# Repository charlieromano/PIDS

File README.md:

<h1> PIDS</h1>

Proyecto PIDS, CESE 2020. 

<h3> Índice </h3>

<hr>

1. [Iniciar Repositorio](#iniciar)

 	1.1. [Clonar repositorio](#clonar)	
 	1.2. [Incluir submódulos](#submodulos)
 	1.3. [Instalar software](#software)
 	
 		1.3.1 [openocd](#openocd)
 		1.3.2 [gcc arm](#gcc)
 		1.3.3 [EDU-CIAA](#educiaa)
 		1.3.4 [Troubleshooting ](#troubleshooting)
 			1.3.4.1 [Troubleshooting gcc-arm](#gcc-arm)
 			1.3.4.2 [Troubleshooting Ubuntu 22](#ubuntu22)
 			1.3.4.3 [Troubleshooting Virtualbox Ubuntu 22 Guest OS](#guestOS)
 			1.3.4.4 [Troubleshooting FTDI driver](#ftdi)
 	
 	1.4. [Crear un programa](#create)
 	1.5. [Seleccionar un programa](#select)

2. [Ejemplos usando UART](#UART)

3. [Ejemplos usando Máquinas de Estado y RTOS](#fsm)

4. [Ejemplos usando Objeto Activo](#ActiveObject)

5. [Ejemplos usando Objeto Activo con Interrupciones](#ActiveObjectISR)

6. [Ejemplos usando Objeto Activo con Interrupciones y UART](#ActiveObjectUART)

<hr>

## Ejemplos usando UART 

Link: https://github.com/charlieromano/PIDS/tree/main/Scripts/UART_RTOS

<hr>

## Ejemplos usando Máquinas de Estado y RTOS  

Link: https://github.com/charlieromano/PIDS/tree/main/Scripts/RTOS_fsm

<hr>

## Ejemplos usando Objeto Activo  

Link: https://github.com/charlieromano/PIDS/tree/main/Scripts/ActiveObject

<hr>

## Ejemplos usando Objeto Activo con Interrupciones  

Link: https://github.com/charlieromano/PIDS/tree/main/Scripts/ActiveObject_ISR_TEC

<hr>

## Ejemplos usando Objeto Activo con Interrupciones y UART 

Link: https://github.com/charlieromano/PIDS/tree/main/Scripts/ActiveObject_ISR_UART

<hr>

## 1. Iniciar Repositorio 

Para ejecutar el software desarrollado en este repositorio hace falta incluir submódulos y también software adicional relacionado a la plataforma EDU-CIAA. Para esto, se explican los pasos:

1. Clonar este repositorio
2. Incluir submódulos
3. Instalar software

### 1.1: Clonar este repositorio 

```bash
git clone https://github.com/charlieromano/PIDS.git
```

### 1.2: Incluir submódulos 

```bash
cd PIDS
cd Scripts
git submodule add https://github.com/epernia/firmware_v3.git    #Agrega firmware_v3 como submodulo
git submodule init
git submodule update

```

### 1.3: Instalar software 

Si tiene todo el software instalado puede saltar a la sección siguiente de Crear un Programa.

#### 1.3.1 Instalar openocd 

```bash
sudo apt install openocd
```

#### 1.3.2 Instalar gcc-arm-none-eab 

```bash
sudo apt install gcc-arm-none-eabi

```
Si todo sale ok saltar a la sección crear programa.

#### 1.3.3  Instalar software EDU-CIAA (opcional) 

Debe descargar de [releases](https://github.com/epernia/software/releases/tag/r1.1.0) la versión para Windows o Linux.

Link: https://github.com/epernia/software/releases/tag/r1.1.0

Descomprimir la carpeta en una ruta conocida, sin espacios y con los permisos adecuados. Se recomiendan:

- **Windows**. C:\CIAA\
- **Linux**. $HOME/CIAA/

Luego ingresar a la carpeta y ejecutar el lanzador de apliaciones. 

#### 1.3.4 Troubleshooting  

#### 1.3.4.1 Troubleshooting gcc-arm-none-eabi 

Este fue el primer fail al intentar compilar un programa con el comando "make download". Para solucionarlo, en la instalación de ubuntu 20 LTS lo que hice fue seguir el siguiente hilo: https://askubuntu.com/questions/1243252/how-to-install-arm-none-eabi-gdb-on-ubuntu-20-04-lts-focal-fossa

Básicamente hice lo siguiente:

```bash
sudo apt remove gcc-arm-none-eabi
```

Download latest version  (Linux x86_64 Tarball) [from their website](https://developer.arm.com/tools-and-software/open-source-software/developer-tools/gnu-toolchain/gnu-rm/downloads), check its MD5. Unpack it into some directory. I used /usr/share/ : 

```bash
sudo tar xjf gcc-arm-none-eabi-your-version.bz2 -C /usr/share/
```

Create links so that binaries are accessible system-wide:

```bash
sudo ln -s /usr/share/<gcc-arm-none-eabi-your-version>/bin/arm-none-eabi-gcc /usr/bin/arm-none-eabi-gcc 
...
```

Para mi instalación, (ubuntu 20 LTS) tuve que ejecutar los siguientes links:

```bash
sudo ln -s /usr/share/gcc-arm-none-eabi-10-2020-q4-major-x86_64-linux/gcc-arm-none-eabi-10-2020-q4-major/bin/arm-none-eabi-gcc /usr/bin/arm-none-eabi-gcc
sudo ln -s /usr/share/gcc-arm-none-eabi-10-2020-q4-major-x86_64-linux/gcc-arm-none-eabi-10-2020-q4-major/bin/arm-none-eabi-g++ /usr/bin/arm-none-eabi-g++
sudo ln -s /usr/share/gcc-arm-none-eabi-10-2020-q4-major-x86_64-linux/gcc-arm-none-eabi-10-2020-q4-major/bin/arm-none-eabi-gdb /usr/bin/arm-none-eabi-gdb
sudo ln -s /usr/share/gcc-arm-none-eabi-10-2020-q4-major-x86_64-linux/gcc-arm-none-eabi-10-2020-q4-major/bin/arm-none-eabi-size /usr/bin/arm-none-eabi-size
sudo ln -s /usr/share/gcc-arm-none-eabi-10-2020-q4-major-x86_64-linux/gcc-arm-none-eabi-10-2020-q4-major/bin/arm-none-eabi-objcopy /usr/bin/arm-none-eabi-objcopy
sudo ln -s /usr/share/gcc-arm-none-eabi-10-2020-q4-major-x86_64-linux/gcc-arm-none-eabi-10-2020-q4-major/bin/arm-none-eabi-objdump /usr/bin/arm-none-eabi-objdump

```

Luego funcionó ok.

**UPDATE**: Para Ubuntu 22 (con arm-none-eabi-10.3-2021.10) completé todos los links a comandos con el siguiente código:

```bash
charlieromano@Toshiba-L845:~/Downloads/PIDS/Scripts/firmware_v3$ ls -l /usr/share/gcc-arm-none-eabi-10.3-2021.10/bin/ | awk '{print "sudo ln -s /usr/share/gcc-arm-none-eabi-10.3-2021.10/bin/"$9"  /usr/bin/"$9}'
```

Con el código resultante, excepto la primera línea, se copian todos los links. Es decir, copiar y pegar en la terminal 

```bash
#sudo ln -s /usr/share/gcc-arm-none-eabi-10.3-2021.10/bin/  /usr/bin/
sudo ln -s /usr/share/gcc-arm-none-eabi-10.3-2021.10/bin/arm-none-eabi-addr2line  /usr/bin/arm-none-eabi-addr2line
sudo ln -s /usr/share/gcc-arm-none-eabi-10.3-2021.10/bin/arm-none-eabi-ar  /usr/bin/arm-none-eabi-ar
sudo ln -s /usr/share/gcc-arm-none-eabi-10.3-2021.10/bin/arm-none-eabi-as  /usr/bin/arm-none-eabi-as
sudo ln -s /usr/share/gcc-arm-none-eabi-10.3-2021.10/bin/arm-none-eabi-c++  /usr/bin/arm-none-eabi-c++
sudo ln -s /usr/share/gcc-arm-none-eabi-10.3-2021.10/bin/arm-none-eabi-c++filt  /usr/bin/arm-none-eabi-c++filt
sudo ln -s /usr/share/gcc-arm-none-eabi-10.3-2021.10/bin/arm-none-eabi-cpp  /usr/bin/arm-none-eabi-cpp
sudo ln -s /usr/share/gcc-arm-none-eabi-10.3-2021.10/bin/arm-none-eabi-elfedit  /usr/bin/arm-none-eabi-elfedit
sudo ln -s /usr/share/gcc-arm-none-eabi-10.3-2021.10/bin/arm-none-eabi-g++  /usr/bin/arm-none-eabi-g++
sudo ln -s /usr/share/gcc-arm-none-eabi-10.3-2021.10/bin/arm-none-eabi-gcc  /usr/bin/arm-none-eabi-gcc
sudo ln -s /usr/share/gcc-arm-none-eabi-10.3-2021.10/bin/arm-none-eabi-gcc-10.3.1  /usr/bin/arm-none-eabi-gcc-10.3.1
sudo ln -s /usr/share/gcc-arm-none-eabi-10.3-2021.10/bin/arm-none-eabi-gcc-ar  /usr/bin/arm-none-eabi-gcc-ar
sudo ln -s /usr/share/gcc-arm-none-eabi-10.3-2021.10/bin/arm-none-eabi-gcc-nm  /usr/bin/arm-none-eabi-gcc-nm
sudo ln -s /usr/share/gcc-arm-none-eabi-10.3-2021.10/bin/arm-none-eabi-gcc-ranlib  /usr/bin/arm-none-eabi-gcc-ranlib
sudo ln -s /usr/share/gcc-arm-none-eabi-10.3-2021.10/bin/arm-none-eabi-gcov  /usr/bin/arm-none-eabi-gcov
sudo ln -s /usr/share/gcc-arm-none-eabi-10.3-2021.10/bin/arm-none-eabi-gcov-dump  /usr/bin/arm-none-eabi-gcov-dump
sudo ln -s /usr/share/gcc-arm-none-eabi-10.3-2021.10/bin/arm-none-eabi-gcov-tool  /usr/bin/arm-none-eabi-gcov-tool
sudo ln -s /usr/share/gcc-arm-none-eabi-10.3-2021.10/bin/arm-none-eabi-gdb  /usr/bin/arm-none-eabi-gdb
sudo ln -s /usr/share/gcc-arm-none-eabi-10.3-2021.10/bin/arm-none-eabi-gdb-add-index  /usr/bin/arm-none-eabi-gdb-add-index
sudo ln -s /usr/share/gcc-arm-none-eabi-10.3-2021.10/bin/arm-none-eabi-gdb-add-index-py  /usr/bin/arm-none-eabi-gdb-add-index-py
sudo ln -s /usr/share/gcc-arm-none-eabi-10.3-2021.10/bin/arm-none-eabi-gdb-py  /usr/bin/arm-none-eabi-gdb-py
sudo ln -s /usr/share/gcc-arm-none-eabi-10.3-2021.10/bin/arm-none-eabi-gprof  /usr/bin/arm-none-eabi-gprof
sudo ln -s /usr/share/gcc-arm-none-eabi-10.3-2021.10/bin/arm-none-eabi-ld  /usr/bin/arm-none-eabi-ld
sudo ln -s /usr/share/gcc-arm-none-eabi-10.3-2021.10/bin/arm-none-eabi-ld.bfd  /usr/bin/arm-none-eabi-ld.bfd
sudo ln -s /usr/share/gcc-arm-none-eabi-10.3-2021.10/bin/arm-none-eabi-lto-dump  /usr/bin/arm-none-eabi-lto-dump
sudo ln -s /usr/share/gcc-arm-none-eabi-10.3-2021.10/bin/arm-none-eabi-nm  /usr/bin/arm-none-eabi-nm
sudo ln -s /usr/share/gcc-arm-none-eabi-10.3-2021.10/bin/arm-none-eabi-objcopy  /usr/bin/arm-none-eabi-objcopy
sudo ln -s /usr/share/gcc-arm-none-eabi-10.3-2021.10/bin/arm-none-eabi-objdump  /usr/bin/arm-none-eabi-objdump
sudo ln -s /usr/share/gcc-arm-none-eabi-10.3-2021.10/bin/arm-none-eabi-ranlib  /usr/bin/arm-none-eabi-ranlib
sudo ln -s /usr/share/gcc-arm-none-eabi-10.3-2021.10/bin/arm-none-eabi-readelf  /usr/bin/arm-none-eabi-readelf
sudo ln -s /usr/share/gcc-arm-none-eabi-10.3-2021.10/bin/arm-none-eabi-size  /usr/bin/arm-none-eabi-size
sudo ln -s /usr/share/gcc-arm-none-eabi-10.3-2021.10/bin/arm-none-eabi-strings  /usr/bin/arm-none-eabi-strings
sudo ln -s /usr/share/gcc-arm-none-eabi-10.3-2021.10/bin/arm-none-eabi-strip  /usr/bin/arm-none-eabi-strip
```

Con esto comenzó a funcionar usando además el troubleshooting para ubuntu 22 de la sección que sigue.

#### 1.3.4.2 Troubleshooting Ubuntu 22  

Error al compilar:

```bash
charlieromano@Toshiba-L845:~/Downloads/PIDS/Scripts/firmware_v3$ make download 
  ../App/out/../App/src/App.o ../App/out/libs/cmsis_core//src/armv7m_startup.o ../App/out/libs/editline//src/editline.o ../App/out/libs/sys_newlib//src/system.o  
DOWNLOAD to FLASH
Open On-Chip Debugger 0.11.0
Licensed under GNU GPL v2
For bug reports, read
	http://openocd.org/doc/doxygen/bugs.html
dap command not exists. Use OLD script
DEPRECATED! use 'adapter driver' not 'interface'
DEPRECATED! use 'adapter speed' not 'adapter_khz'
scripts/openocd/lpc4337_old.cfg:121: Error: target requires -dap parameter instead of -chain-position!
in procedure 'script' 
at file "embedded:startup.tcl", line 26
at file "scripts/openocd/lpc4337.cfg", line 37
at file "scripts/openocd/lpc4337_old.cfg", line 121
make: *** [Makefile:296: .download_flash] Error 1

```

Link a la solución: https://groups.google.com/g/embebidos32/c/yFN8wUIiS0s

Al parecer en la última actualización se deprecaron algunos comandos. Se reemplazan en el archivo lpc4337_old.cfg.

```bash
charlieromano@Toshiba-L845:~/Downloads/PIDS/Scripts/firmware_v3$ find -name lpc4337_old.cfg
./scripts/openocd/lpc4337_old.cfg
charlieromano@Toshiba-L845:~/Downloads/PIDS/Scripts/firmware_v3$ cd scripts/openocd/
charlieromano@Toshiba-L845:~/Downloads/PIDS/Scripts/firmware_v3/scripts/openocd$ vim lpc4337_old.cfg 

```

En el siguiente extracto de código están los comandos que se deben reemplazar.

```bash
# Utilizar una interface tipo FTDI, todo lo que sigue está basado en ello
######################################################################################################
#interface ftdi
adapter driver ftdi

#.
#.
#.

################################################################
# Especifica en KHz la frecuencia del Clock en el JTAG (TCK)
################################################################
transport select jtag
#adapter_khz 2000
adapter speed 2000

#.
#.
#.

################################################################
# Creo los 2 targets lpc4337.m4 y lpc4337.m0
################################################################
#target create $_CHIPNAME.m4 cortex_m -chain-position $_CHIPNAME.m4
#target create $_CHIPNAME.m0 cortex_m -chain-position $_CHIPNAME.m0
dap create $_CHIPNAME.m4.dap -chain-position $_CHIPNAME.m4
target create $_CHIPNAME.m4 cortex_m -dap $_CHIPNAME.m4.dap
```

Con esto volvió a funcionar. 

#### 1.3.4.3 Ubuntu 22 como Virtualbox Guest OS 

Seguir los siguientes pasos:

* conectar EDU-CIAA

* virtualbox settings: 

  * Serial Ports: Enable Port 1 
    * Port Number: COM1
    * Port Mode: Host Device (Conncet to existing pipe/socket)
    * Path/Address: COM3
  * Serial Ports: Enable Port 2
    * Port Number: COM2
    * Port Mode: Host Device (Conncet to existing pipe/socket)
    * Path/Address: COM4

* instalar cutecom en Guest OS

  * iniciar como superuser
  * conectar Device: /dev/ttyS1

* OK

Referencia: https://maker.pro/linux/projects/how-to-use-a-hosts-serial-port-from-a-guest-in-virtualbox

#### 		1.3.4.4  Troubleshooting FTDI driver 

Este troubleshooting sirve para configurar y utilizar una maquina virtual Ubuntu 22.04 (guest OS) sobre Windows (Host) usando Virtualbox. El error del compilador cuando se intenta descargar un programa a la placa es ***"Error: unable to open ftdi device with vid 0403, pid 6010, description '', serial '' at bus location '*'"*** 

```makefile
charlieromano@Ubuntu22:~/Downloads/PIDS/Scripts/firmware_v3$ make download 

../App/out/../App/src/App.o ../App/out/libs/cmsis_core//src/armv7m_startup.o ../App/out/libs/editline//src/editline.o ../App/out/libs/sys_newlib//src/system.o  

DOWNLOAD to FLASH

Open On-Chip Debugger 0.11.0

Licensed under GNU GPL v2

For bug reports, read

	http://openocd.org/doc/doxygen/bugs.html

dap command not exists. Use OLD script

Error: no device found

Error: unable to open ftdi device with vid 0403, pid 6010, description '*', serial '*' at bus location '*'

make: *** [Makefile:296: .download_flash] Error 1

```

Esto se debe a que no hay una correcta configuracion de los drivers USB. Se deben seguir las referencias. En device manager debe aparecer en Universal Serial Bus devices el driver Dual RS232-HS:

Una vez verificados estos pasos, en la virtual machine hace falta activar el driver desde la interfaz de virtualbox. Ver en la imagen el boton USB abajo a la derecha:

Con este driver FTDI Dual RS232-HS activado, volver a ejectura el make download. Con esto funciona OK.

**References**:

- Foro: https://groups.google.com/g/embebidos32/c/cZ0JRElbmHU/m/wD15QAjoDAAJ
- Zadig: https://zadig.akeo.ie/#
- FTDI: https://ftdichip.com/drivers/vcp-drivers/

## 4. Crear un programa 

Ir al directorio del repositorio, y luego desde el submodule firmware_v3 crear un program folder:

```bash
cd PIDS
cd firmware_v3          #Entras al repo del firmware_v3
make new_program        #Ejecutas el script para crear nuevo programa
```

Se debe abrir un cuadro de diálogo como el siguiente:

```bash
PIDS/firmware_v3$ make new_program 
  ../ISR_test/out/../ISR_test/src/ISR_test.o ../ISR_test/out/libs/cmsis_core//src/armv7m_startup.o ../ISR_test/out/libs/editline//src/editline.o ../ISR_test/out/libs/sys_newlib//src/system.o  

User preferences found in file: /home/charlieromano/Documents/Academico/CESE/PIDS/firmware_v3/scripts/user/user_preferences.cfg
 - Programs folder: ..
 - Author full name: Ing. Carlos German Carreño Romano
 - Author e-mail: ccarreno@fi.uba.ar
 - License: bsd-2-clause

New program wizard starting...

Program created on folder: ..
 - Name: ISR_test
 - Version: 1.0
 - Template: c
Selected as program to compile in program.mk
```

Luego se puede chequear el árbol del proyecto, en este caso el proyecto se llama ISR_test:

```bash
CESE/PIDS/firmware_v3$ tree -L 2 ../ISR_test/
../ISR_test/
├── config.mk
├── inc
│   └── ISR_test.h
├── ISR_test
│   └── src
├── LICENSE.txt
├── out
│   ├── ISR_test.bin
│   ├── ISR_test.elf
│   ├── ISR_test.map
│   ├── libs
│   └── linker-params
└── src
    └── ISR_test.c

6 directories, 8 files
```

Con este programa se puede compilar y descargar a la placa con make download:

```bash
CESE/PIDS/firmware_v3$ make download 
  ../ISR_test/out/../ISR_test/src/ISR_test.o ../ISR_test/out/libs/cmsis_core//src/armv7m_startup.o ../ISR_test/out/libs/editline//src/editline.o ../ISR_test/out/libs/sys_newlib//src/system.o  
CC ISR_test.c
LD params
LD ../ISR_test/out/ISR_test.elf...
COPY ISR_test.elf TO ISR_test.bin
DOWNLOAD to FLASH
Open On-Chip Debugger 0.10.0
Licensed under GNU GPL v2
For bug reports, read
	http://openocd.org/doc/doxygen/bugs.html
dap command not exists. Use OLD script
adapter speed: 2000 kHz
none separate
cortex_m reset_config vectreset
Info : clock speed 2000 kHz
Info : JTAG tap: lpc4337.m4 tap/device found: 0x4ba00477 (mfg: 0x23b (ARM Ltd.), part: 0xba00, ver: 0x4)
Info : JTAG tap: lpc4337.m0 tap/device found: 0x0ba01477 (mfg: 0x23b (ARM Ltd.), part: 0xba01, ver: 0x0)
Info : lpc4337.m4: hardware has 6 breakpoints, 4 watchpoints
Info : lpc4337.m0: hardware has 2 breakpoints, 1 watchpoints
auto erase enabled
wrote 8192 bytes from file ../ISR_test/out/ISR_test.bin in 0.350298s (22.838 KiB/s)
Info : JTAG tap: lpc4337.m4 tap/device found: 0x4ba00477 (mfg: 0x23b (ARM Ltd.), part: 0xba00, ver: 0x4)
Info : JTAG tap: lpc4337.m0 tap/device found: 0x0ba01477 (mfg: 0x23b (ARM Ltd.), part: 0xba01, ver: 0x0)
Warn : Only resetting the Cortex-M core, use a reset-init event handler to reset any peripherals or configure hardware srst support.
Warn : Only resetting the Cortex-M core, use a reset-init event handler to reset any peripherals or configure hardware srst support.
shutdown command invoked

```

## Seleccionar un programa de este repo 

El archivo que se debe modificar corresponde al firmware_v3 y se llama "program.mk". El árbol del repo (submodule) es el siguiente:

```bash
charlieromano@ToshibaL845:~/PIDS/firmware_v3$ tree -L 1
.
├── compile_commands.json
├── documentation
├── examples
├── libs
├── LICENSE
├── Makefile
├── program.mk
├── README.md
├── scripts
├── templates
└── test

6 directories, 5 files
charlieromano@ToshibaL845:~/PIDS/firmware_v3$ cat program.mk 

```

y su contenido se muestra a continuación:

```makefile
#==============================================================================
# This file select a program to compile with make
#==============================================================================

# ---------- Example of path -------------------------------------------
# Program path
#(relative to this folder, leave void if the program is in this folder)
#PROGRAM_PATH = examples_c/sapi/gpio
# Program name
#PROGRAM_NAME = blinky

# ---------- Your paths: -----------------------------------------------

PROGRAM_PATH = ..
PROGRAM_NAME = UART
~                      
```

En este ejemplo en PROGRAM_PATH se define el directorio padre donde reside el file, y el nombre del programa elegido es UART. Luego se compila con "make download" y se ejecuta:

```bash
charlieromano@ToshibaL845:~/PIDS/firmware_v3$ make download 
  ../UART/out/../UART/src/UART.o ../UART/out/libs/cmsis_core//src/armv7m_startup.o ../UART/out/libs/editline//src/editline.o ../UART/out/libs/sys_newlib//src/system.o  
DOWNLOAD to FLASH
Open On-Chip Debugger 0.10.0
Licensed under GNU GPL v2
For bug reports, read
	http://openocd.org/doc/doxygen/bugs.html
dap command not exists. Use OLD script
adapter speed: 2000 kHz
none separate
cortex_m reset_config vectreset
Info : clock speed 2000 kHz
Info : JTAG tap: lpc4337.m4 tap/device found: 0x4ba00477 (mfg: 0x23b (ARM Ltd.), part: 0xba00, ver: 0x4)
Info : JTAG tap: lpc4337.m0 tap/device found: 0x0ba01477 (mfg: 0x23b (ARM Ltd.), part: 0xba01, ver: 0x0)
Info : lpc4337.m4: hardware has 6 breakpoints, 4 watchpoints
Info : lpc4337.m0: hardware has 2 breakpoints, 1 watchpoints
target halted due to debug-request, current mode: Handler External Interrupt(26)
xPSR: 0x2100002a pc: 0x1a001216 msp: 0x10007fb8
auto erase enabled
wrote 16384 bytes from file ../UART/out/UART.bin in 0.546994s (29.251 KiB/s)
Info : JTAG tap: lpc4337.m4 tap/device found: 0x4ba00477 (mfg: 0x23b (ARM Ltd.), part: 0xba00, ver: 0x4)
Info : JTAG tap: lpc4337.m0 tap/device found: 0x0ba01477 (mfg: 0x23b (ARM Ltd.), part: 0xba01, ver: 0x0)
Warn : Only resetting the Cortex-M core, use a reset-init event handler to reset any peripherals or configure hardware srst support.
Warn : Only resetting the Cortex-M core, use a reset-init event handler to reset any peripherals or configure hardware srst support.
shutdown command invoked

```

Este programa se inicializa con una frase que dice "usb". Si se le envía algún caracter por la conexión serie, se enciende el led verde y amarillo.

<hr>

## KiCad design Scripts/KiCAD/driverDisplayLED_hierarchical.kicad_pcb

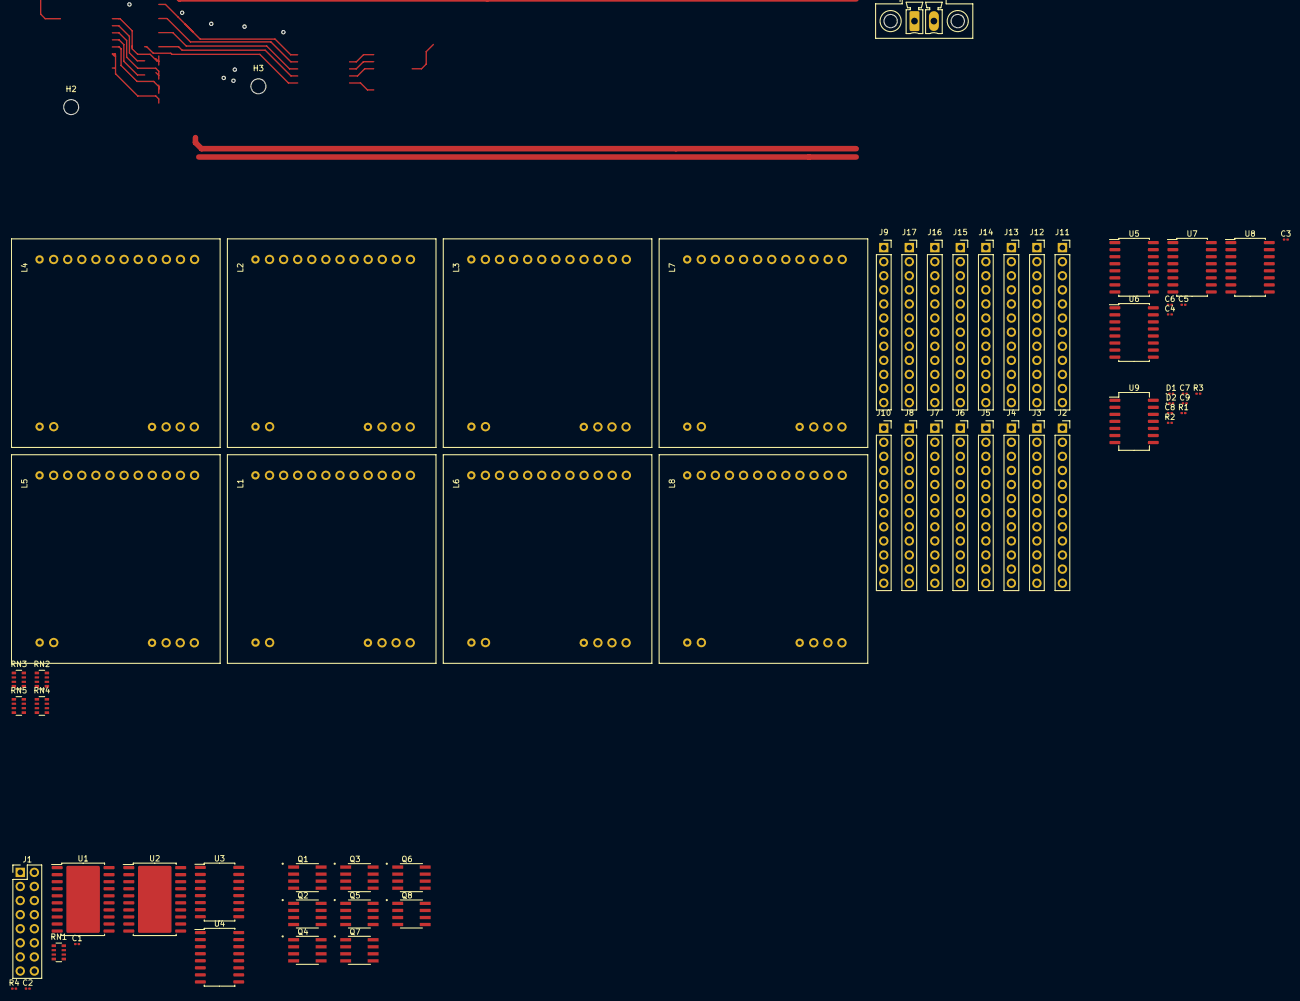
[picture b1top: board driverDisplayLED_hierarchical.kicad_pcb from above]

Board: 2 copper layers, 69 parts (0 on the bottom side), 100 nets.

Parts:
C1, C2, C3, C4, C5, C6, C7, C8, C9: C; C_0201_0603Metric
D1, D2: D; D_0201_0603Metric
H1, H2, H3, H4, H5, H6: MountingHole; MountingHole_2.7mm_M2.5_ISO14580
J1: Conn_02x08_Counter_Clockwise; PinHeader_2x08_P2.54mm_Vertical
J2, J3, J4, J5, J6, J7, J8, J9, J10, J11, J12, J13, J14, J15, J16, J17: Conn_01x12_Male; PinSocket_1x12_P2.54mm_Vertical
J19: Conn_01x02_Female; PhoenixContact_MCV_1,5_2-GF-3.5_1x02_P3.50mm_Vertical_Threa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
L1, L2, L3, L4, L5, L6, L7, L8: LedMatrix_M; 1588AB-24
Q1, Q2, Q3, Q4, Q5, Q6, Q7, Q8: FDS4953; SOIC127P600X175-8N
R1, R2, R3: R; R_0201_0603Metric
R4: 0; R_0201_0603Metric
RN1: R_Network04; R_Array_Convex_4x0603
RN2, RN3, RN4, RN5: 50; R_Array_Convex_4x0603
U1, U2: 74HC245; SO-20-1EP_7.52x12.825mm_P1.27mm_EP6.045x12.09mm_Mask3.56x4.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
U3, U4: 74HC138D; SO-16_5.3x10.2mm_P1.27mm
U5, U6, U7, U8: 74HC595; SO-16_5.3x10.2mm_P1.27mm
U9: 74HC04; SO-14_5.3x10.2mm_P1.27mm

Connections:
/Decoders/B0-b5: J1.10, U1.18
/Decoders/B1-a5: J1.9, U1.17
/Decoders/B2-b6: J1.12, U1.16
/Decoders/B3-a6: J1.11, U1.15
/Decoders/B4-b7: J1.14, U1.14
/Decoders/B5B6B7-b8: J1.16, U1.11, U1.12, U1.13
/Decoders/a4-A5: J1.7, U2.7
/ShiftRegs/RCLK: U5.12, U6.12, U7.12, U8.12
A1: J1.2, R1.2, U2.3
A1_SER: U1.3, U5.14
A5_SRCLK: U1.7, U5.11, U6.11, U7.11, U8.11
E1: U3.4, U9.4, U9.5
E3: U4.6, U9.6
GND: C1.1, C2.1, C3.1, C4.1, C5.1, C6.1, C8.2, C9.2, D1.2, J1.1, J1.3, J1.5, J1.15, J3.1, J3.2, J3.3, J3.4, J3.5, J3.6, J3.7, J3.8, J5.1, J5.2, J5.3, J5.4, J5.5, J5.6, J5.7, J5.8, J7.1, J7.2, J7.3, J7.4, J7.5, J7.6, J7.7, J7.8, J9.1, J9.2, J9.3, J9.4, J9.5, J9.6, J9.7, J9.8, J11.1, J11.2, J11.3, J11.4, J11.5, J11.6, J11.7, J11.8, J13.1, J13.2, J13.3, J13.4, J13.5, J13.6, J13.7, J13.8, J15.1, J15.2, J15.3, J15.4, J15.5, J15.6, J15.7, J15.8, J17.1, J17.2, J17.3, J17.4, J17.5, J17.6, J17.7, J17.8, J19.1, R2.2, R3.2, RN1.1, RN2.1, RN3.1, RN4.1, RN5.1, U1.1, U1.10, U1.19, U2.10, U3.8, U4.8, U5.8, U5.13, U6.8, U6.13, U7.8, U7.13, U8.8, U8.13, U9.7
Ha1: J2.12, J6.12, J10.12, J14.12, L1.12, L3.12, L5.12, L7.12, Q8.7, Q8.8, RN5.5
Ha2: J2.11, J6.11, J10.11, J14.11, L1.11, L3.11, L5.11, L7.11, Q8.5, Q8.6, RN5.4
Ha3: J2.10, J6.10, J10.10, J14.10, L1.10, L3.10, L5.10, L7.10, Q6.7, Q6.8, RN5.3
Ha4: J2.9, J6.9, J10.9, J14.9, L1.9, L3.9, L5.9, L7.9, Q6.5, Q6.6, RN5.2
Ha5: J3.9, J7.9, J11.9, J15.9, Q2.5, Q2.6, RN4.2
Ha6: J3.10, J7.10, J11.10, J15.10, Q2.7, Q2.8, RN4.3
Ha7: J3.11, J7.11, J11.11, J15.11, Q4.5, Q4.6, RN4.4
Ha8: J3.12, J7.12, J11.12, J15.12, Q4.7, Q4.8, RN4.5
Hb1: J4.12, J8.12, J12.12, J16.12, L2.12, L4.12, L6.12, L8.12, RN3.5
Hb2: J4.11, J8.11, J12.11, J16.11, L2.11, L4.11, L6.11, L8.11, RN3.4
Hb3: J4.10, J8.10, J12.10, J16.10, L2.10, L4.10, L6.10, L8.10, RN3.3
Hb4: J4.9, J8.9, J12.9, J16.9, L2.9, L4.9, L6.9, L8.9, RN3.2
Hb5: J5.9, J9.9, J13.9, J17.9, Q1.5, Q1.6, RN2.2
Hb6: J5.10, J9.10, J13.10, J17.10, Q1.7, Q1.8, RN2.3
Hb7: J5.11, J9.11, J13.11, J17.11, Q3.5, Q3.6, RN2.4
Hb8: J5.12, J9.12, J13.12, J17.12, Q3.7, Q3.8, RN2.5
Hb11: Q7.7, Q7.8
Hb12: Q7.5, Q7.6
Hb13: Q5.7, Q5.8
Hb14: Q5.5, Q5.6
L1R1: J2.8, J4.8, L1.8, L2.8, U5.7
L1R2: J2.7, J4.7, L1.7, L2.7, U5.6
L1R3: J2.6, J4.6, L1.6, L2.6, U5.5
L1R4: J2.5, J4.5, L1.5, L2.5, U5.4
L1R5: J2.4, J4.4, L1.4, L2.4, U5.3
L1R6: J2.3, J4.3, L1.3, L2.3, U5.2
L1R7: J2.2, J4.2, L1.2, L2.2, U5.1
L1R8: J2.1, J4.1, L1.1, L2.1, U5.15
L3R1: J6.8, J8.8, L3.8, L4.8, U6.7
L3R2: J6.7, J8.7, L3.7, L4.7, U6.6
L3R3: J6.6, J8.6, L3.6, L4.6, U6.5
L3R4: J6.5, J8.5, L3.5, L4.5, U6.4
L3R5: J6.4, J8.4, L3.4, L4.4, U6.3
L3R6: J6.3, J8.3, L3.3, L4.3, U6.2
L3R7: J6.2, J8.2, L3.2, L4.2, U6.1
L3R8: J6.1, J8.1, L3.1, L4.1, U6.15
L5R1: J10.8, J12.8, L5.8, L6.8, U7.7
L5R2: J10.7, J12.7, L5.7, L6.7, U7.6
L5R3: J10.6, J12.6, L5.6, L6.6, U7.5
L5R4: J10.5, J12.5, L5.5, L6.5, U7.4
L5R5: J10.4, J12.4, L5.4, L6.4, U7.3
L5R6: J10.3, J12.3, L5.3, L6.3, U7.2
L5R7: J10.2, J12.2, L5.2, L6.2, U7.1
L5R8: J10.1, J12.1, L5.1, L6.1, U7.15
L7R1: J14.8, J16.8, L7.8, L8.8, U8.7
L7R2: J14.7, J16.7, L7.7, L8.7, U8.6
L7R3: J14.6, J16.6, L7.6, L8.6, U8.5
L7R4: J14.5, J16.5, L7.5, L8.5, U8.4
L7R5: J14.4, J16.4, L7.4, L8.4, U8.3
L7R6: J14.3, J16.3, L7.3, L8.3, U8.2
L7R7: J14.2, J16.2, L7.2, L8.2, U8.1
L7R8: J14.1, J16.1, L7.1, L8.1, U8.15
unnamed: C7.1, U9.2
unnamed: C7.2, D1.1, D2.2
unnamed: C8.1, D2.1, R3.1, U9.3
unnamed: J1.4, U2.4
unnamed: J1.6, U2.5
unnamed: J1.8, U2.6
unnamed: R1.1, R2.1, U9.1
unnamed: R4.2, U2.2
unnamed: RN1.2, U1.8
unnamed: U2.13, U3.5, U4.5
unnamed: U2.14, U3.6, U4.4
unnamed: U2.15, U3.3, U4.3
unnamed: U2.16, U3.2, U4.2
unnamed: U2.17, U3.1, U4.1
unnamed: U5.9, U6.14
unnamed: U6.9, U7.14
unnamed: U7.9, U8.14
VCC: C1.2, C2.2, C3.2, C4.2, C5.2, C6.2, C9.1, J19.2, Q1.1, Q1.3, Q2.1, Q2.3, Q3.1, Q3.3, Q4.1, Q4.3, Q5.1, Q5.3, Q6.1, Q6.3, Q7.1, Q7.3, Q8.1, Q8.3, R4.1, U1.20, U2.1, U2.20, U3.16, U4.16, U5.10, U5.16, U6.10, U6.16, U7.10, U7.16, U8.10, U8.16, U9.14
Ya0: Q2.4, U4.15
Ya1: Q2.2, U4.14
Ya2: Q4.4, U4.13
Ya3: Q4.2, U4.12
Ya4: Q6.4, U4.11
Ya5: Q6.2, U4.10
Ya6: Q8.4, U4.9
Ya7: Q8.2, U4.7
Yb0: Q1.4, U3.15
Yb1: Q1.2, U3.14
Yb2: Q3.4, U3.13
Yb3: Q3.2, U3.12
Yb4: Q5.4, U3.11
Yb5: Q5.2, U3.10
Yb6: Q7.4, U3.9
Yb7: Q7.2, U3.7

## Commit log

2021-03-07 Repo init
2021-03-07 add KICAD project
2021-03-07 Add Documents
2021-03-07 Added firmware_v3 repo
2021-05-02 updating Repo to old Master branch
2021-05-02 updating Repo to old Master branch step by step
2021-05-02 actualizo README
2021-05-02 reinit submodule
2021-05-02 submodule firmware_v3
2021-05-03 working from scratch at ubuntu 20
2021-05-03 add parsing files for captures
2021-05-10 ejemplo UART tx rx con interrupciones OK
2021-05-16 Datasheets folder
2021-05-16 KiCAD: LED driver U4: 74hc245D CE to GND
2021-05-23 inicio esquemáticos de la placa de control
2021-05-23 placa de control: esquemático
2021-05-24 fixing GNDs
2021-05-24 mounting holes
2021-05-25 reordenand esquematico a partir de modulos
2021-05-26 reorganizo, completo subcircuitos, preparo para el LQFP64
2021-05-26 agrego multisheet
2021-05-26 comenzando Conector de salida
2021-05-27 Added processDiagram.drawio
2021-05-30 continuo esquematico Placa de Control
2021-09-01 add .tex draft
2021-09-01 changing Figures by Pics
2021-09-01 Added blockDiagram.drawio
2021-09-02 Added blockDiagram.png
2021-09-02 add blocDiagram to Tesis .tex
2021-09-16 short update charter.tex
2021-09-19 Added sniffingDiagram.drawio
2021-09-20 agrego diagramas de los ensayos con analizador lógico.
2021-09-27 adding updates to document
2021-09-30 adding more pictures after meeting
2021-10-04 update firmware_v3 repo
2021-10-05 actualizo el README incluyendo ejecucion del repo
2021-10-08 cleaning UART_RTOS project
2021-10-08 UART echo working with RTOS
2021-10-09 UART_RTOS update
2021-10-11 Tx/Rx using xQueue @UART_RTOS
2021-10-11 UART_RTOS: Queue update to receiving from multiple sources using xDataFrame at main.h
2022-01-14 reorganizo el repo con estructura normalizada
2022-01-16 working on fsm for reading dataframe streaming
2022-01-19 working on fsmDataframes
2022-01-19 agrego codigo fsmTest con tres estados, usando input stream y argc, argv
2022-01-19 working on fsmTest
2022-01-27 working on fsmTest.c: tres estados, maquina de estados simple en C
2022-02-01 update del firmware v3
2022-02-02 documentando UART_RTOS readme
2022-02-05 se suben updates de documentación: README del UART_RTOS y texto en Tesis.
2022-02-06 agrego tareas usando vTaskDelayUntil() para imprimir en la UART usando el mismo prototipo
2022-02-06 Update fsmDataframes
2022-02-06 actualizo el ejemplo UART_RTOS con tres opciones de tareas: eco, two tasks, two senders and one receiver
2022-02-06 Update fsmDataframes diagram
2022-02-06 actualizo con el ejemplo fsmTest.c y su documentación en el README de RTOS_fsm
2022-02-06 update README UART_RTOS
2022-02-06 RTOS_fsm: ejemplo usando statemachine test con RTOS
2022-02-06 RTOS_fsm: funcionando, actualizo README
2022-02-07 statemachineTCN: comienzo implementación de fsm para streaming de datos entrantes
2022-02-17 agrego Scripts/Activeobject
2022-02-20 update 2022-02-20
2022-02-20 agrego ejemplo ActiveObject working
2022-02-20 ActiveObject: dos máquinas de estado funcionando en conjunto
2022-02-20 actualizo README de ActiveObject
2022-02-28 actualizo ActiveObject cambiando prioridades entre tareas TA y TB, actualizo README
2022-03-01 agrego ejemplo antibouncingAO en construcción
2022-03-01 antibouncingAO: funcionando con timers y TEC1, presionando 1 seg cambia de estado
2022-03-01 antibouncingAO: agrego interrupciones de TEC1
2022-03-01 antibouncingAO rename to ActiveObject_ISR_TEC
2022-03-02 ActiveObject_ISR_UART: funcionando con Statemachine AB y UART_RECEIVE por interrupción. Prende el LED3(Verde) cuando le enviamos un caracter, y se desactive el callback
2022-03-06 README update
2022-03-06 ActiveObject: update README
2022-03-06 ActiveObjectISR_TEC: update README
2022-03-07 Kicad: driverDisplay update fila B SER pin
2022-03-13 ActiveObject_ISR_UART: libero interrupty reinicializo en la tarea Handler usando un nuevo semaforo, xSemaphoreUART
2022-03-21 ActiveObject_UART: working on receiver task
2022-03-21 ActiveObject_UART: receive and dispatch after IRQ_Handler and process data at vTask
2022-03-24 add TCN PIDS frame datasheet
2022-03-26 actualizo Tesis
2022-04-03 ActiveObjectISR: antibouncing using ISR working ok.
2022-04-04 update UART handler code
2022-04-06 ActiveObject_UART: adding PIDS state machine template
2022-04-10 Added planoPIDS.diagram.io
2022-04-18 displayLED: starting driver
2022-04-21 ActiveObject_UART update. DisplayLED WIP.
2022-04-21 ActiveObject_UART update.
2022-04-24 ActiveObject_UART: taskUART receiving into data buffer, with timer displaying its content
2022-05-09 add displayLED update in portmap.h and displayLED.c; also uploading Oscilloscope captures
2022-05-31 testing chained vTaskDelayUntil()
2022-06-09 displayLED: adding display_clock_array at displayLED.c
2022-06-15 displayLED: first good tests on displayLED, see videos 2022-06-15
2022-06-21 displayLED: correcting code, first nice videos sending incremental numericl data
2022-07-12 displayLED: updating code working as in the 2022-07-11 google videos
2022-08-04 refactoring displayLED.c
2022-08-04 refactoring displayLED.c: using external memory bank, test_data[].
2022-08-04 update.
2022-08-12 adding CASE 2022 final article
2022-08-14 actualizo README con troubleshooting para Ubuntu 22
2022-08-14 update README: troubleshooting para ubuntu 22
2022-08-15 agrego poster CASE 2022 en IEEE
2022-09-02 AppRTOS: template for final documentation
2022-09-04 Update Tesis: Memoria, makeindex
2022-09-04 AppRTOS: displayLED working again.
2022-09-12 memoria: update del chapter 1
2022-10-10 pequeños updates en cap1 de la memoria
2022-10-29 updating local folders
2022-10-29 updating Pics folders
2022-10-31 working in user defined functions udf.c
2022-10-31 udf.c: working matrix transpose at reshapeDisplay()
2022-11-05 udf.c: testing via ./testPrint.o
2022-11-13 udf.c, testingSequences.c: working in matrix reshape for display conversions
2022-11-13 testingSequences.c: buffer_out for display tested. Case 0,1,2 OK.
2022-11-14 testingSequences.c: buffer_out for display tested. Case 0,1,2,3 OK.
2022-11-14 matrices user defined functions documentation
2022-11-28 Docs: diagramas y update de figuras en memoria
2022-12-05 working on memoria.tex
2022-12-11 working on Tesis: Chapter 1 ended.
2023-04-07 Trabajando en la redaccion de la tesis. Update Marzo 2023.
2023-04-07 Writing: Ch.3, Requerimientos y Casos de uso
2023-04-09 README: Truobleshooting con Virtulabox Ubuntu 22 GuestOS
2023-04-09 README: update
2023-04-09 README: Troubleshooting FTDI drivers con Ubuntu 22.04 as Guest OS using Virtualbox in Windows host
2023-04-09 update pics in readme
2023-04-16 STATE MACHINE DISPLAY LED: updating states and events
2023-04-16 state machine display
2023-04-17 figura logica display
2023-04-17 logica display con f1, f2, f3
2023-04-17 codigo logica para procesar datos display
2023-04-18 displayLed.c y statemachine_displayLed.c compiling but not tested
2023-04-20 displayLed.c: tested with RTOS task and serial output. log.displayLedTest.txt
2023-04-20 state machine display led: correcting fsmDisplayLed name in active object (userTasks.c). Compiling and tested OK.
2023-04-20 writing implementation logic for display handlers to get data using buffers
2023-04-21 Updating Tesis: Chap 3
2023-04-30 AppDynMem: app demo con memoria dinamica. Implementa un buffer de largo maximo "buf_len" y lo usa para leer y escribir por puerto serie usando malloc() y free() de freeRTOS.
2023-05-01 Update Tesis: Ch.3 Desarrollo. Secciones de maquina de estado, objeto activo, RTOS y overview de la implementacion.
2023-05-01 udf.c:update for testing messages using printf with no RTOS at Scripts folder
2023-05-02 avance en modelo de maquina de estados para displayled
2023-05-12 correcciones memoria, cap. 3
2023-05-18 updating AppRTOS: statemachine_displayLED. Testing state by state
2023-05-23 Update AppRTOS: for loop for STATE_DISPLAY_ENCODING tested
2023-05-24 AppRTOS: using dynamic Memory and state machine for displayLed encoding
2023-05-25 Update AppRTOS: displayled.c statemachine_displayled.c vTaskTest. Task test generates the message event to allow the statemachine to display next message.
2023-05-27 AppRTOS: tested on display. Video 2023-05-27 4:03 p.m.
2023-05-28 Adding UART to AppRTOS
2023-05-30 Deleting redundant dependencies. Update AppRTOS, displayLed and statemachine_displayled with MITRE-TIGRE messages
2023-05-30 AppRTOS, UART, config.mk Update for including Interrupts. Tested UART_IRQ interrupt! OK
2023-05-30 AppRTOS: StateMachine_UART added and tested from main using interrupts. Pattern: ISR -> callback -> semaphore <- vHandlerUART -> vTaskUART
2023-06-04 Memoria: update Componentes de Sistema y Cartel LED
2023-06-05 statemachine UART updates
2023-06-12 Updates unvalidated on statemachine UART.c
2023-06-22 AppRTOS: update statemachine, working but error from button queue arising ([] Error sending data to the queueHandle_button␍␊ []Function not implemented␊)
2023-06-22 update tesis: chap. 3, displayLed
2023-07-08 Updates on memoria
2023-07-10 updates in statemachine_UART, statemachine_PIDS
2023-07-10 updates in memoria
2023-07-16 Update statemachineUART.c: handler idle working with state error
2023-07-24 Update AppRTOS: adding inter Task communication between fsmUART and fsmPIDS. Successful. An extra file will be needed to define the inter communication structure. This file has to include the resourc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
2023-07-27 update AppRTOS: create common.h and update the statemachine_PIDS
2023-08-24 update Tesis: incluyo explicación memoria dinámica y reordeno secciones
2023-08-27 Update Memoria: edición del resumen
2023-08-28 update MEmoria: redacción capítulo 2
2023-09-19 correcciones capitulo 1
2023-09-20 Correcciones version 1 actualizadas
2023-10-02 Update caps 2 y 3
2023-10-05 update imagenes
2023-10-05 imagenes
2023-10-15 Update: hasta capítulo 3 revisado.
2023-10-16 Update tesis: cap 3, seccion display Led.
2023-10-19 Update memoria: redacción revisada hasta capítulo 3 inclusive.
2023-10-19 Figuras
2023-10-23 Update cap 4
2023-10-27 Update correcciones y revisiones capítulo 3.
2023-11-01 enviado revisión y capítulos 4, 5 en modo borrador.
2023-11-02 Capítulo 5 para corregir. Capítulo 4 aún en redacción.
2023-11-02 Update compiled
2023-11-10 Update: revisión y correcciones caps 4 y 5. Falta revisar figuras.
2023-11-13 update code for testing display led
2023-11-13 update versión final de memoria con imagenes actualizadas.
